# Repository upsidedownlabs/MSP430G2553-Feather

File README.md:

# MSP430G2553 Feather Board

MSP430G2553 based Adafruit feather compatible board 🪶

| Front              |  Back |
| :-------------------------: | :-------------------------: |
|   |  |

<!-- |Pinout|
| :--: |
|| -->

| Dimensions              |  Schematic |
| :-------------------------: | :-------------------------: |
| 53.05 x 22.90 mm  |  |

## License

#### Hardware
CERN Open Hardware License Version 2 - Strongly Reciprocal ([CERN-OHL-S-2.0](https://spdx.org/licenses/CERN-OHL-S-2.0.html)).

#### Software
MIT open source [license](http://opensource.org/licenses/MIT).

#### Documentation:
<br />This work is licensed under a <a rel="license" href="http://creativecommons.org/licenses/by/4.0/">Creative Commons Attribution 4.0 International License</a>.

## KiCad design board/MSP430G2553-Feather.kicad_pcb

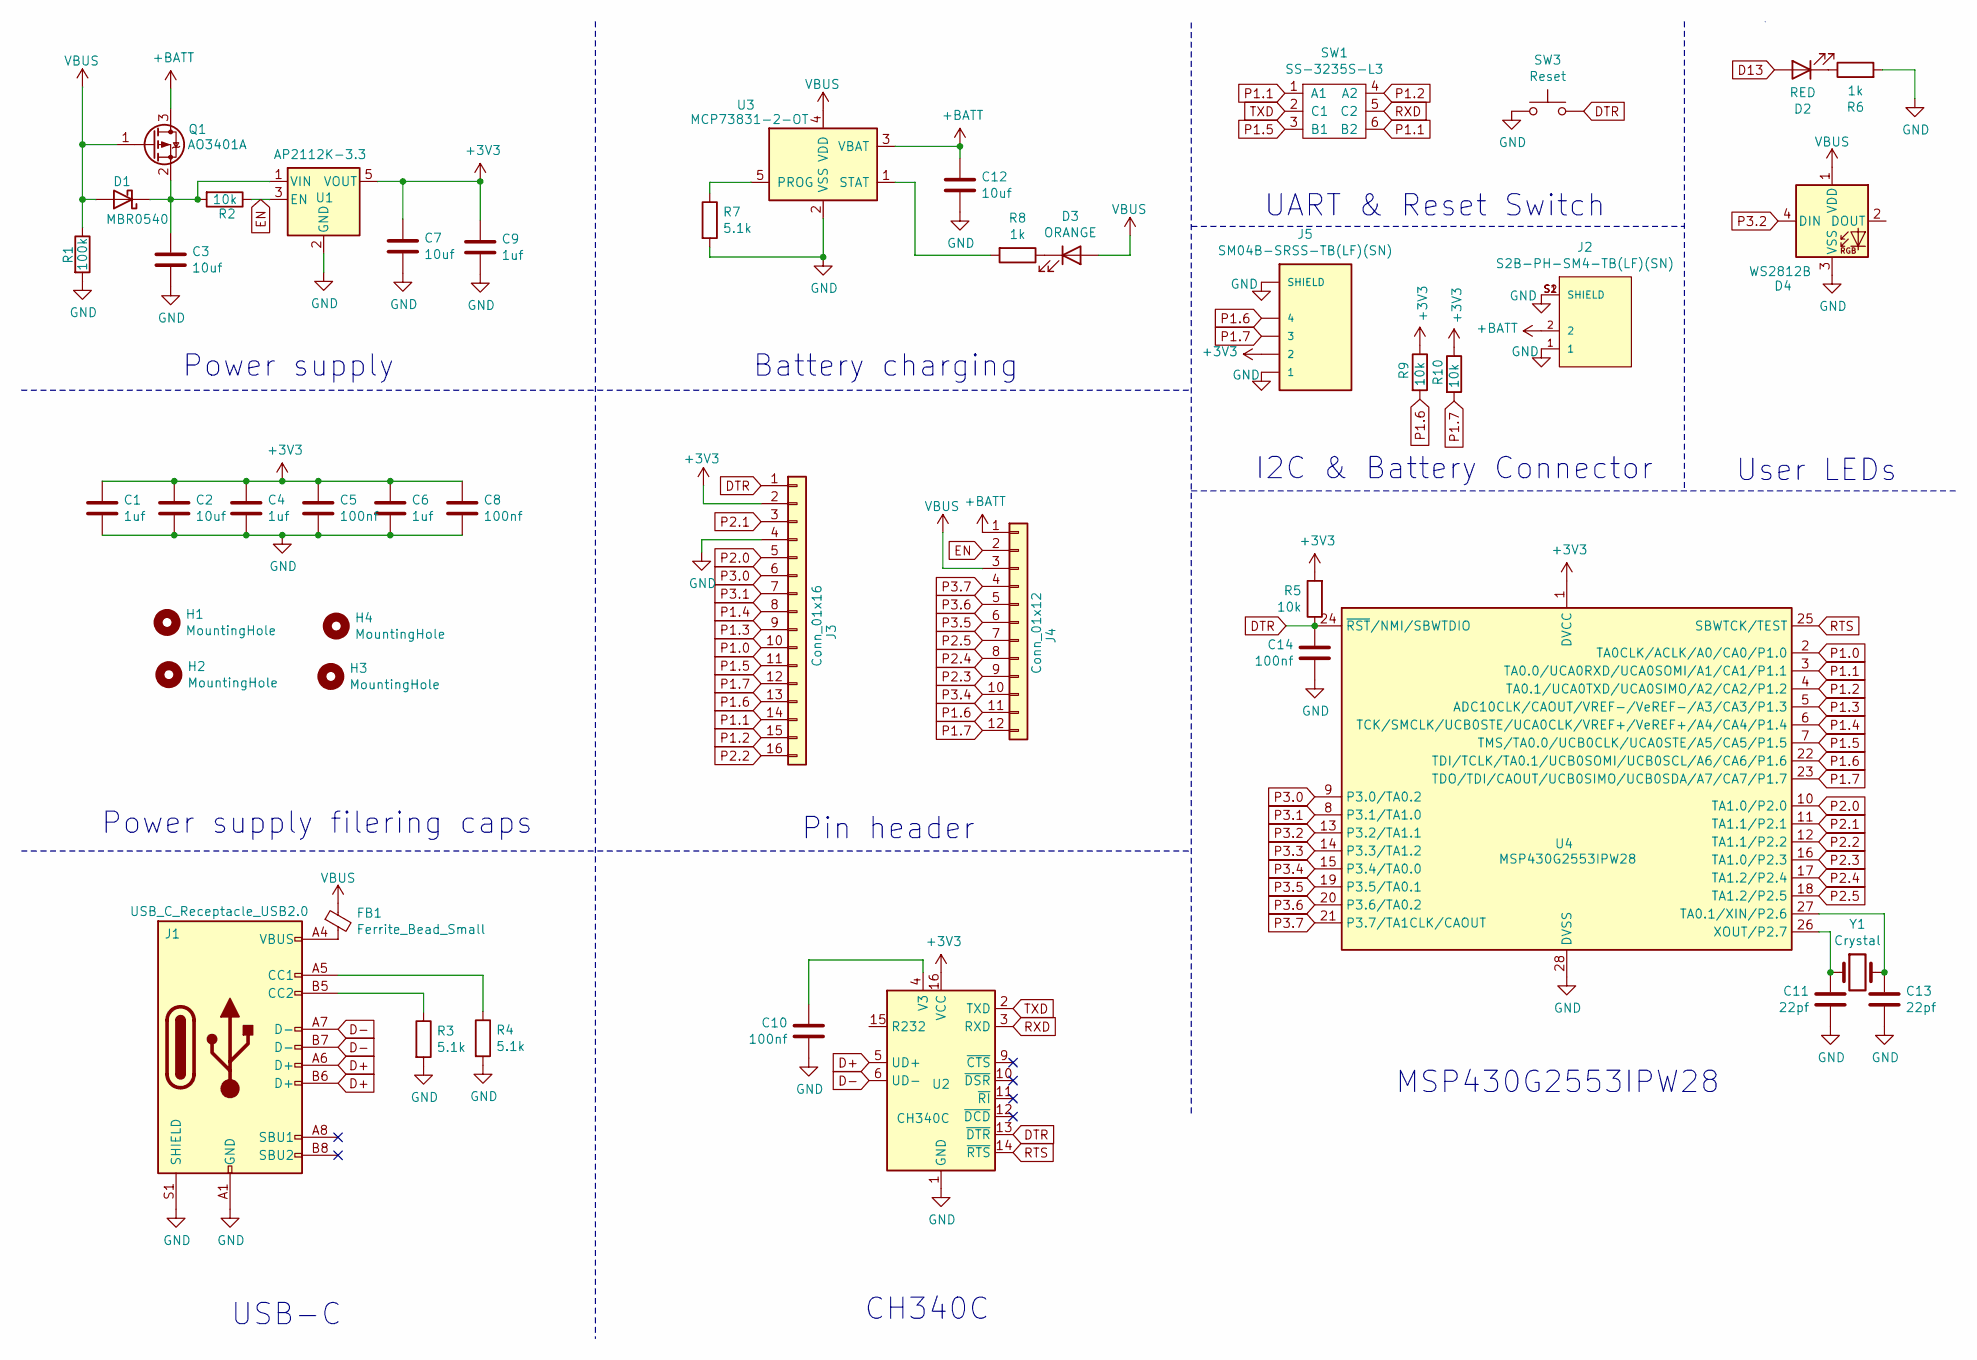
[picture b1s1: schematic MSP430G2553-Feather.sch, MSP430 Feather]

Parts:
C1, C4, C6, C9: 1uf; C_0603_1608Metric
C2, C3, C7: 10uf; C_0805_2012Metric
C5, C8, C10, C14: 100nf; C_0603_1608Metric
C11, C13: 22pf; C_0603_1608Metric
C12: 10uf; C_0603_1608Metric
D1: MBR0540; D_SOD-123
D2: RED; LED_0805_2012Metric
D3: ORANGE; LED_0805_2012Metric
D4: WS2812B; LED_WS2812B_PLCC4_5.0x5.0mm_P3.2mm
FB1: Ferrite_Bead_Small; L_0805_2012Metric
H1, H2: MountingHole; MountingHole_2.5mm
H3, H4: MountingHole; MountingHole_2.5mm_Pad
J1: USB_C_Receptacle_USB2.0; USB_C_Receptacle_HRO_TYPE-C-31-M-12
J2: S2B-PH-SM4-TB(LF)(SN); JST_S2B-PH-SM4-TB(LF)(SN)
J3: Conn_01x16; PinHeader_1x16_P2.54mm_Vertical
J4: Conn_01x12; PinHeader_1x12_P2.54mm_Vertical
J5: SM04B-SRSS-TB(LF)(SN); JST_SM04B-SRSS-TB(LF)(SN)
Q1: AO3401A; SOT-23
R1: 100k; R_0603_1608Metric
R2, R5, R9, R10: 10k; R_0603_1608Metric
R3, R4, R7: 5.1k; R_0603_1608Metric
R6, R8: 1k; R_0603_1608Metric
SW1: SS-3235S-L3
SW3: Reset; SW_SPST_SKQG_WithStem
U1: AP2112K-3.3; SOT-23-5
U2: CH340C; SOIC-16_3.9x9.9mm_P1.27mm
U3: MCP73831-2-OT; SOT-23-5
U4: MSP430G2553IPW28; TSSOP-28_4.4x9.7mm_P0.65mm
Y1: Crystal; Crystal_SMD_3215-2Pin_3.2x1.5mm

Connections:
+3V3: C1.1, C2.1, C4.1, C5.1, C6.1, C7.1, C8.1, C9.1, J3.2, J5.2, R5.2, R9.1, R10.1, U1.5 (VOUT), U2.16 (VCC), U4.1 (DVCC)
+BATT: C12.1, J2.2, J4.1, Q1.3 (D), U3.3 (VBAT)
D13: D2.2 (A)
D+: J1.A6 (D+), J1.B6 (D+), U2.5 (UD+)
D-: J1.A7 (D-), J1.B7 (D-), U2.6 (UD-)
DTR: C14.2, J3.1, R5.1, SW3.2, U2.13 (~DTR), U4.24 (~RST~/NMI/SBWTDIO)
EN: J4.2, R2.1, U1.3 (EN)
GND: C1.2, C2.2, C3.2, C4.2, C5.2, C6.2, C7.2, C8.2, C9.2, C10.1, C11.1, C12.2, C13.2, C14.1, D4.3 (VSS), J1.A1 (GND), J1.A12 (GND), J1.B1 (GND), J1.B12 (GND), J1.S1 (SHIELD), J2.1, J2.S1 (SHIELD), J2.S2 (SHIELD), J3.4, J5.1, J5.S1 (SHIELD), J5.S2 (SHIELD), R1.2, R3.2, R4.2, R6.2, R7.2, SW3.1, U1.2 (GND), U2.1 (GND), U3.2 (VSS), U4.28 (DVSS)
unnamed: C3.1, D1.1 (K), Q1.2 (S), R2.2, U1.1 (VIN)
unnamed: C10.2, U2.4 (V3)
unnamed: C11.2, U4.26 (XOUT/P2.7), Y1.1
unnamed: C13.1, U4.27 (TA0.1/XIN/P2.6), Y1.2
unnamed: D2.1 (K), R6.1
unnamed: D3.1 (K), R8.1
unnamed: FB1.2, J1.A4 (VBUS), J1.A9 (VBUS), J1.B4 (VBUS), J1.B9 (VBUS)
unnamed: J1.A5 (CC1), R4.1
unnamed: J1.B5 (CC2), R3.1
unnamed: R7.1, U3.5 (PROG)
unnamed: R8.2, U3.1 (STAT)
P1.0: J3.10, U4.2 (TA0CLK/ACLK/A0/CA0/P1.0)
P1.1: J3.14, SW1.1 (A1), SW1.6 (B2), U4.3 (TA0.0/UCA0RXD/UCA0SOMI/A1/CA1/P1.1)
P1.2: J3.15, SW1.4 (A2), U4.4 (TA0.1/UCA0TXD/UCA0SIMO/A2/CA2/P1.2)
P1.3: J3.9, U4.5 (ADC10CLK/CAOUT/VREF-/VeREF-/A3/CA3/P1.3)
P1.4: J3.8, U4.6 (TCK/SMCLK/UCB0STE/UCA0CLK/VREF+/VeREF+/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)
P1.5: J3.11, SW1.3 (B1), U4.7 (TMS/TA0.0/UCB0CLK/UCA0STE/A5/CA5/P1.5)
P1.6: J3.13, J4.11, J5.4, R9.2, U4.22 (TDI/TCLK/TA0.1/UCB0SOMI/UCB0SCL/A6/CA6/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)
P1.7: J3.12, J4.12, J5.3, R10.2, U4.23 (TDO/TDI/CAOUT/UCB0SIMO/UCB0SDA/A7/CA7/P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)
P2.0: J3.5, U4.10 (TA1.0/P2.0)
P2.1: J3.3, U4.11 (TA1.1/P2.1)
P2.2: J3.16, U4.12 (TA1.1/P2.2)
P2.3: J4.9, U4.16 (TA1.0/P2.3)
P2.4: J4.8, U4.17 (TA1.2/P2.4)
P2.5: J4.7, U4.18 (TA1.2/P2.5)
P3.0: J3.6, U4.9 (P3.0/TA0.2)
P3.1: J3.7, U4.8 (P3.1/TA1.0)
P3.2: D4.4 (DIN), U4.13 (P3.2/TA1.1)
P3.3: U4.14 (P3.3/TA1.2)
P3.4: J4.10, U4.15 (P3.4/TA0.0)
P3.5: J4.6, U4.19 (P3.5/TA0.1)
P3.6: J4.5, U4.20 (P3.6/TA0.2)
P3.7: J4.4, U4.21 (P3.7/TA1CLK/CAOUT)
RTS: U2.14 (~RTS), U4.25 (SBWTCK/TEST)
RXD: SW1.5 (C2), U2.3 (RXD)
TXD: SW1.2 (C1), U2.2 (TXD)
VBUS: D1.2 (A), D3.2 (A), D4.1 (VDD), FB1.1, J4.3, Q1.1 (G), R1.1, U3.4 (VDD)

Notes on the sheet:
User LEDs
I2C & Battery Connector
UART & Reset Switch
Battery charging
Power supply
Power supply filering caps
Pin header
CH340C
USB-C
MSP430G2553IPW28

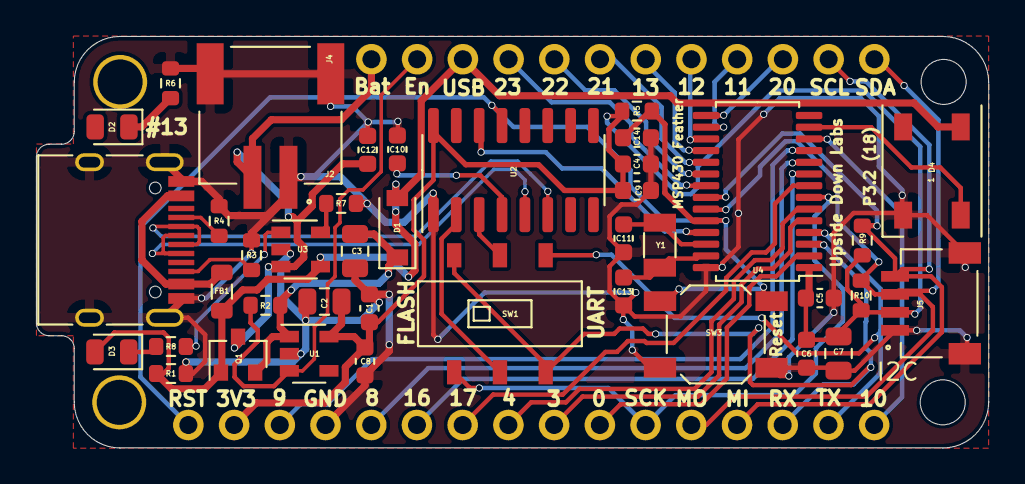
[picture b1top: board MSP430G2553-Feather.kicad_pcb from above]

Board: 2 copper layers, 52.9 x 22.9 mm, 46 parts (0 on the bottom side), 43 nets.

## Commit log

2021-02-22 upload MSP430G2554 Feather board KiCAD files
2021-02-22 Add license
2021-02-22 MSP430G2553 Feather v0.1 back
2021-02-22 MSP430G2553 Feather v0.1 front
2021-02-22 MSP430G2553 Feather v0.1 schematic
2021-02-22 MSP430G2553 Feather v0.1 dimensions
2021-02-22 add MSP430G2553 Feather Schematic
